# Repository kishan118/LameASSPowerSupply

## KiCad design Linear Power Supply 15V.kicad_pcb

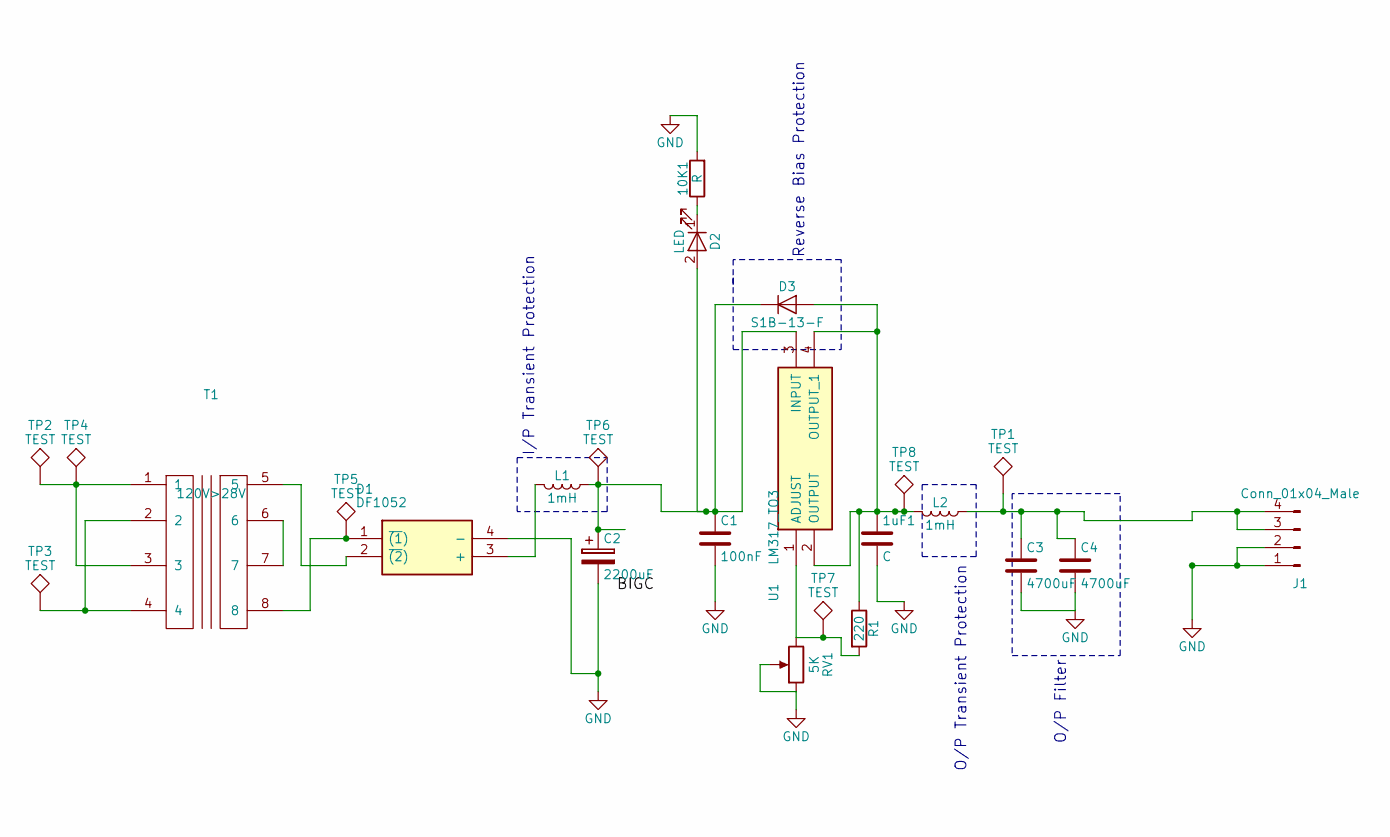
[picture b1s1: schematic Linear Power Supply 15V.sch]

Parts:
1uF1: C; C_0805
10K1: R; R_0805
C1: 100nF; C_0805
C2: 2200uF; CP_Radial_D16.0mm_P7.50mm
C3, C4: 4700uF; CP_Radial_D12.5mm_P5.00mm
D1: DF1052; SOP510P1015X260-4N
D2: LED; LED_0603_HandSoldering
D3: S1B-13-F; D_SMA
J1: Conn_01x04_Male; Pin_Header_Angled_1x04_Pitch2.54mm
L1, L2: 1mH; 2324-V-RC
R1: 220; R_0805
RV1: 5K; Potentiometer_Trimmer_Suntan_TSR-3386C_Vertical
T1: 120V>28V; DIP-8_1
TP1, TP4, TP5, TP6, TP7, TP8: TEST; Measurement_Point_Round-SMD-Pad_Big
TP2, TP3: TEST; MountingHole_4.3mm_M4_DIN965_Pad
U1: LM317_TO3; SOT230P700X180-4N

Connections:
GND: 1uF1.2, 10K1.2, C1.2, C2.2, C3.2, C4.2, D1.4 (-), J1.1, J1.2, RV1.1, RV1.2
unnamed: 1uF1.1, D3.2 (A), L2.2, R1.1, TP8.1, U1.2 (OUTPUT), U1.4 (OUTPUT_1)
unnamed: 10K1.1, D2.1 (K)
unnamed: C1.1, C2.1, D2.2 (A), D3.1 (K), L1.1, TP6.1, U1.3 (INPUT)
unnamed: C3.1, C4.1, J1.3, J1.4, L2.1, TP1.1
unnamed: D1.1 (~(1)), T1.8, TP5.1
unnamed: D1.2 (~(2)), T1.5
unnamed: D1.3 (+), L1.2
unnamed: R1.2, RV1.3, TP7.1, U1.1 (ADJUST)
unnamed: T1.1, T1.3, TP2.1, TP4.1
unnamed: T1.2, T1.4, TP3.1
unnamed: T1.6, T1.7

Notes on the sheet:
I/P Transient Protection
Reverse Bias Protection
O/P Transient Protection
O/P Filter

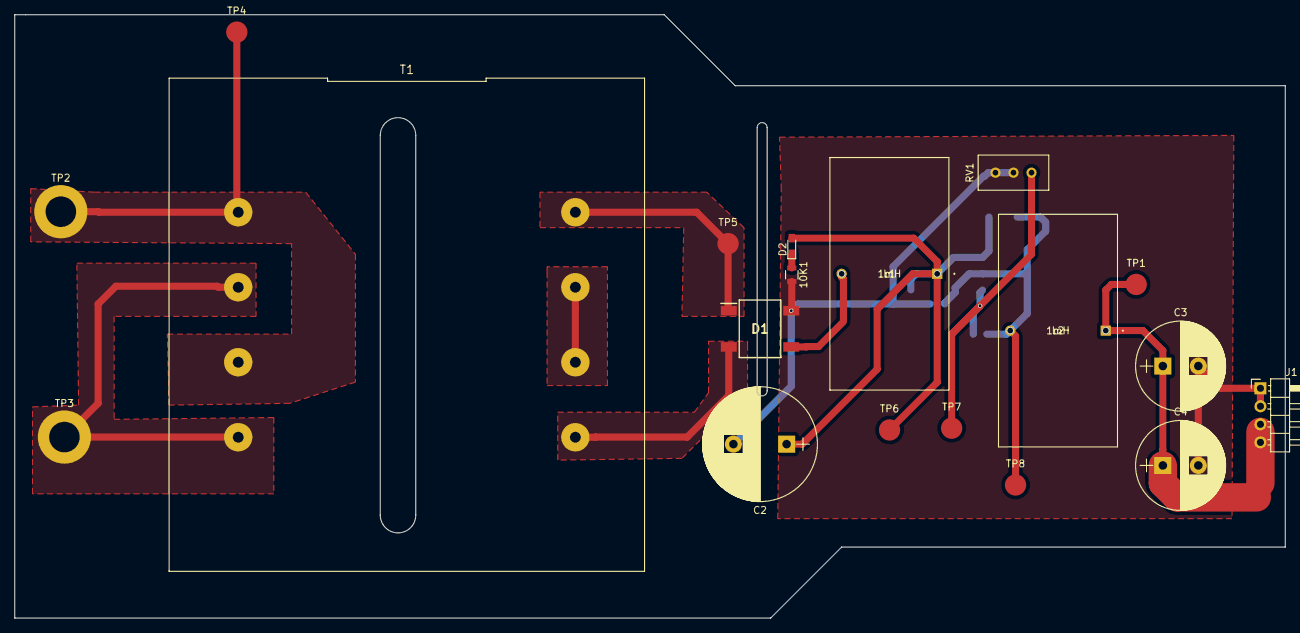
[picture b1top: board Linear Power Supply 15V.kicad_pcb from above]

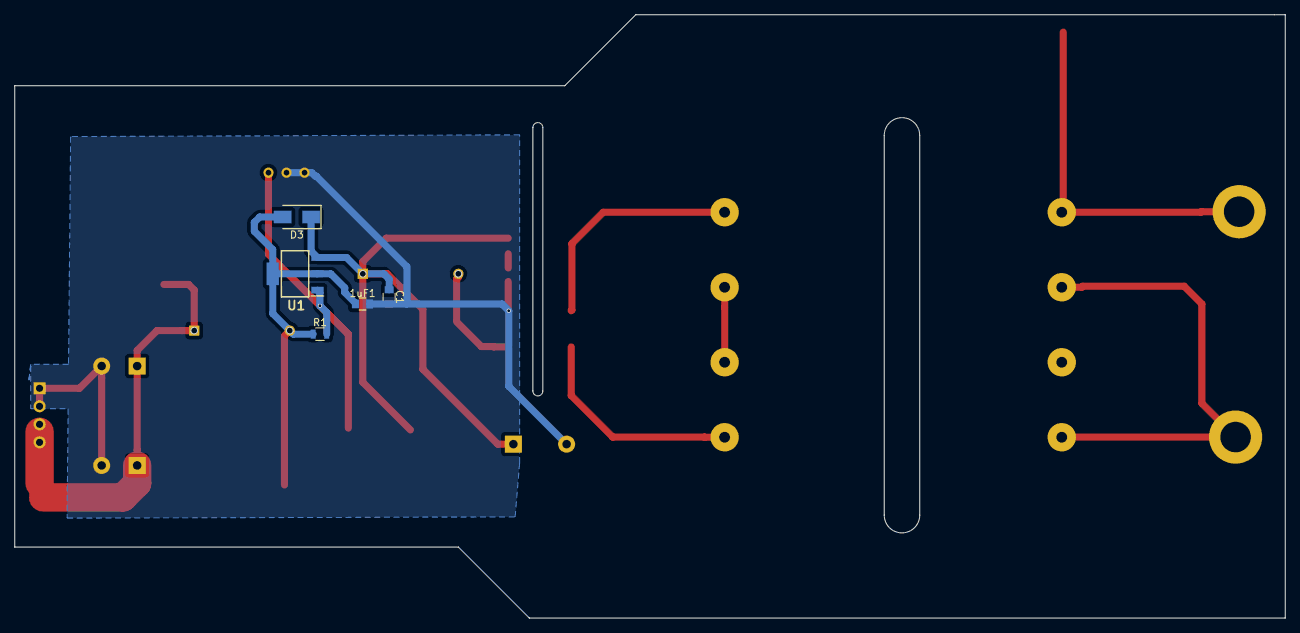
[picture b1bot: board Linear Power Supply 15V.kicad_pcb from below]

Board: 2 copper layers, 179.0 x 85.0 mm, 24 parts (5 on the bottom side), 12 nets.

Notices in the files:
parts and their libraries:
Copyright 2016 Accelerated Designs. All rights reserved.
